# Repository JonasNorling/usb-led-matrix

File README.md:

A USB connected LED matrix
==========================

This is a quick holidays project from 2020/2021. It is a 8×8 SMD LED matrix board with a STM32G4 and USB-C connector.

What it does is up to the software but currently I use it to display CPU load on my PC. When not connected to a USB host it displays a calm animation.

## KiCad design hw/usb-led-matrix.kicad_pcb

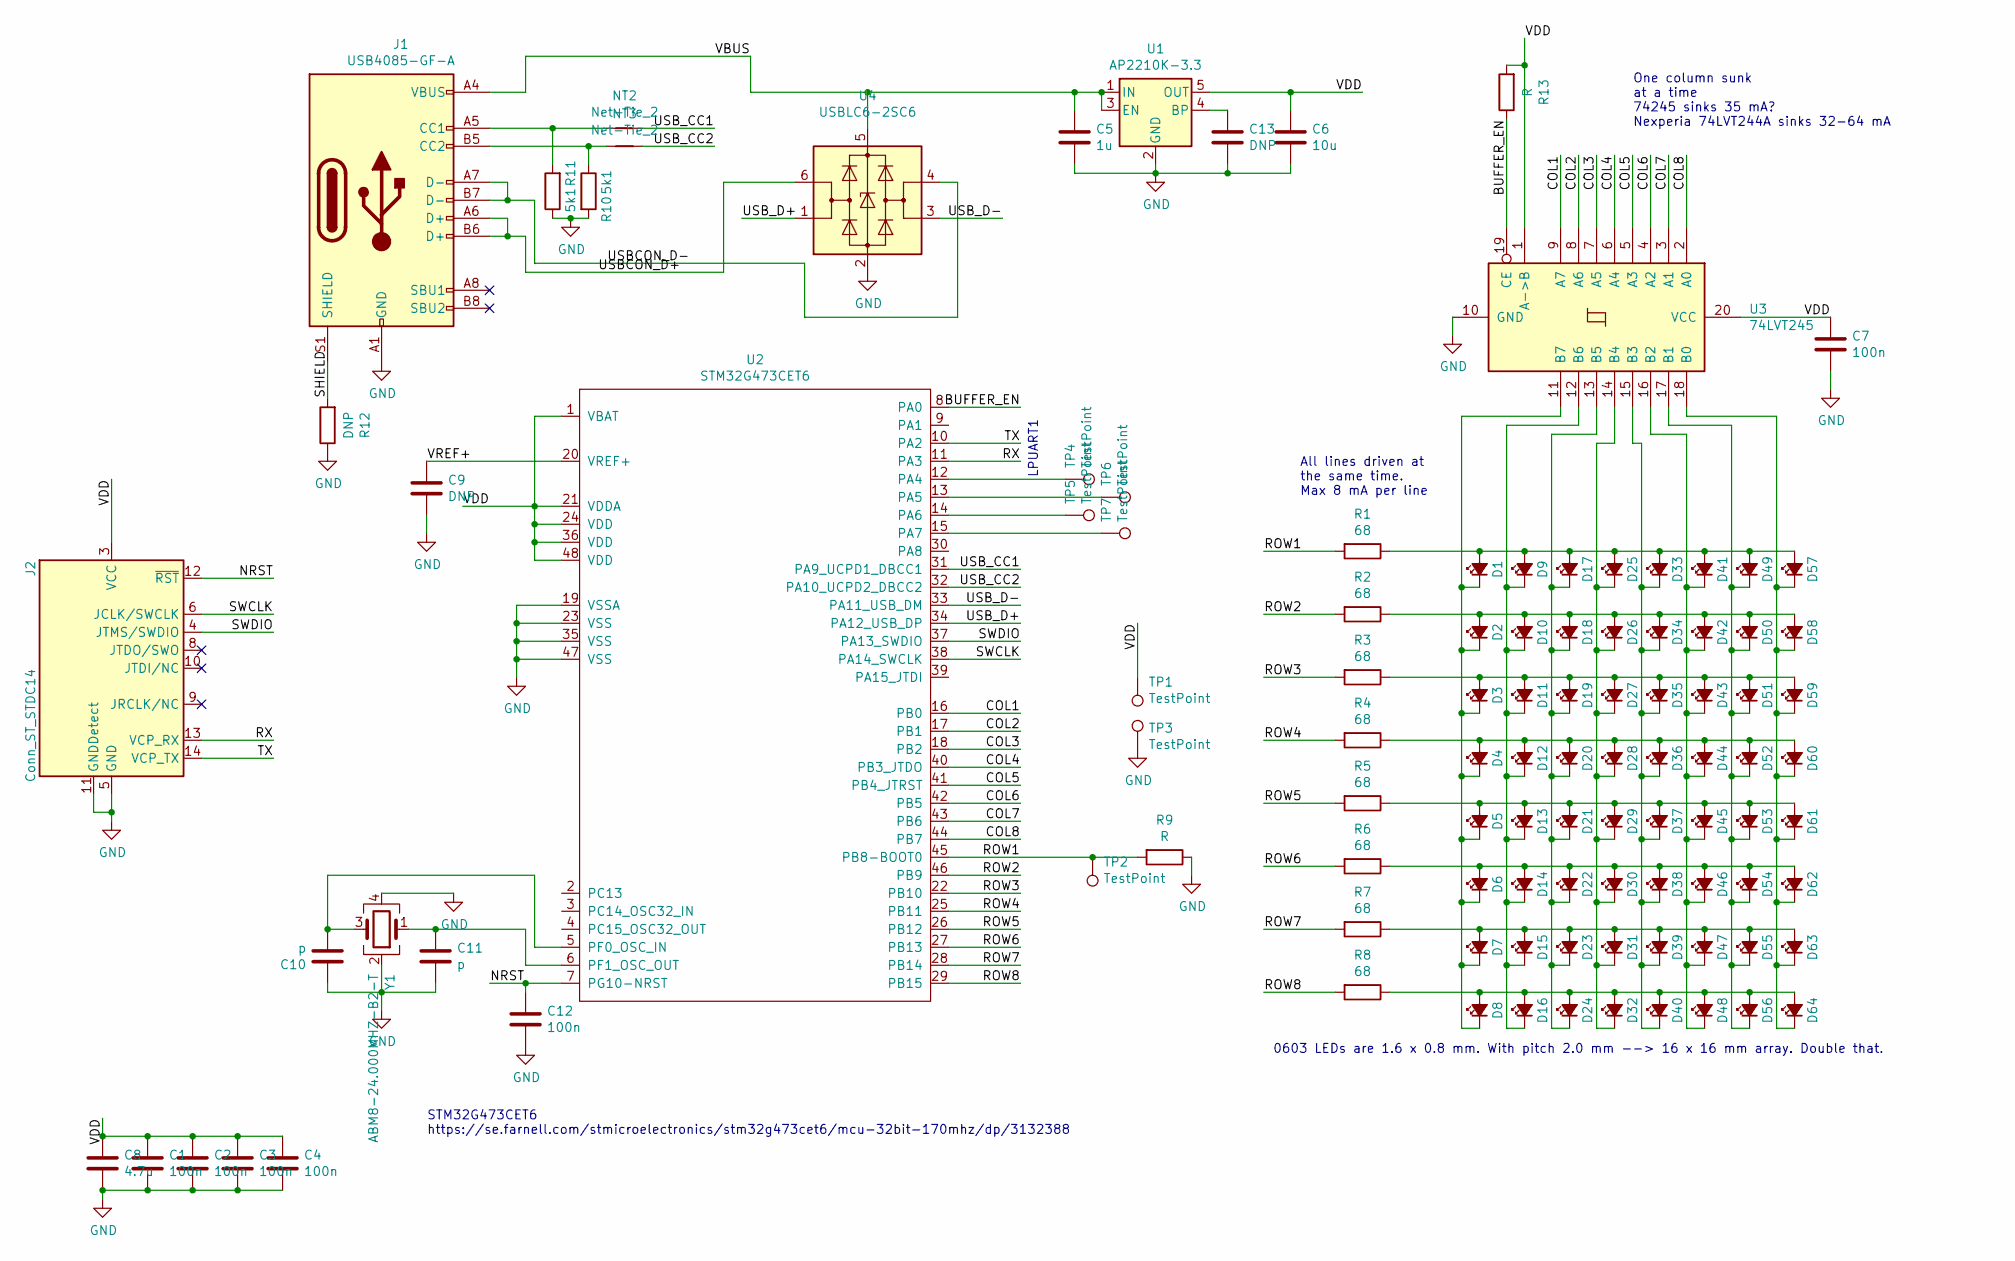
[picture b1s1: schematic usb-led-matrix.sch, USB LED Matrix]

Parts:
C1, C2, C3, C4, C7, C12: 100n; C_0402_1005Metric_Pad0.74x0.62mm_HandSolder
C5: 1u; C_0603_1608Metric_Pad1.08x0.95mm_HandSolder
C6: 10u; C_0603_1608Metric_Pad1.08x0.95mm_HandSolder
C8: 4.7u; C_0603_1608Metric_Pad1.08x0.95mm_HandSolder
C9, C13: DNP; C_0402_1005Metric_Pad0.74x0.62mm_HandSolder
C10, C11: p; C_0402_1005Metric_Pad0.74x0.62mm_HandSolder
D1, D2, D3, D4, D5, D6, D7, D8, D9, D10, D11, D12, D13, D14, D15, D16, D17, D18, D19, D20, D21, D22, D23, D24, D25, D26, D27, D28, D29, D30, D31, D32, D33, D34, D35, D36, D37, D38, D39, D40, D41, D42, D43, D44, D45, D46, D47, D48, D49, D50, D51, D52, D53, D54, D55, D56, D57, D58, D59, D60, D61, D62, D63, D64: LED_Small_ALT; LED_0603_1608Metric
J1: USB4085-GF-A; USB_C_Receptacle_GCT_USB4085
J2: Conn_ST_STDC14; PinHeader_2x07_P1.27mm_Vertical_SMD
NT2, NT3: Net-Tie_2; R_0201_0603Metric
R1, R2, R3, R4, R5, R6, R7, R8: 68; R_0402_1005Metric_Pad0.72x0.64mm_HandSolder
R9, R13: R; R_0402_1005Metric_Pad0.72x0.64mm_HandSolder
R10, R11: 5k1; R_0402_1005Metric_Pad0.72x0.64mm_HandSolder
R12: DNP; R_0402_1005Metric_Pad0.72x0.64mm_HandSolder
TP1, TP2, TP3: TestPoint; TestPoint_THTPad_D1.0mm_Drill0.5mm
TP4, TP5, TP6, TP7: TestPoint; TestPoint_Pad_1.0x1.0mm
U1: AP2210K-3.3; SOT-23-5
U2: STM32G473CET6; LQFP-48_7x7mm_P0.5mm
U3: 74LVT245; TSSOP-20_4.4x6.5mm_P0.65mm
U4: USBLC6-2SC6; SOT-23-6
Y1: ABM8-24.000MHZ-B2-T; Crystal_SMD_3225-4Pin_3.2x2.5mm

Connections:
/BUFFER_EN: R13.1, U2.8 (PA0), U3.19 (CE)
/COL1: U2.16 (PB0), U3.9 (A7)
/COL2: U2.17 (PB1), U3.8 (A6)
/COL3: U2.18 (PB2), U3.7 (A5)
/COL4: U2.40 (PB3_JTDO), U3.6 (A4)
/COL5: U2.41 (PB4_JTRST), U3.5 (A3)
/COL6: U2.42 (PB5), U3.4 (A2)
/COL7: U2.43 (PB6), U3.3 (A1)
/COL8: U2.44 (PB7), U3.2 (A0)
/NRST: C12.1, J2.12 (~RST), U2.7 (PG10-NRST)
/ROW1: R1.2, R9.2, TP2.1, U2.45 (PB8-BOOT0)
/ROW2: R2.2, U2.46 (PB9)
/ROW3: R3.2, U2.22 (PB10)
/ROW4: R4.2, U2.25 (PB11)
/ROW5: R5.2, U2.26 (PB12)
/ROW6: R6.2, U2.27 (PB13)
/ROW7: R7.2, U2.28 (PB14)
/ROW8: R8.2, U2.29 (PB15)
/RX: J2.13 (VCP_RX), U2.11 (PA3)
/SHIELD: J1.S1 (SHIELD), R12.2
/SWCLK: J2.6 (JCLK/SWCLK), U2.38 (PA14_SWCLK)
/SWDIO: J2.4 (JTMS/SWDIO), U2.37 (PA13_SWDIO)
/TX: J2.14 (VCP_TX), U2.10 (PA2)
/USBCON_D+: J1.A6 (D+), J1.B6 (D+), U4.6 (I/O1)
/USBCON_D-: J1.A7 (D-), J1.B7 (D-), U4.4 (I/O2)
/USB_CC1: NT2.2, U2.31 (PA9_UCPD1_DBCC1)
/USB_CC2: NT3.2, U2.32 (PA10_UCPD2_DBCC2)
/USB_D+: U2.34 (PA12_USB_DP), U4.1 (I/O1)
/USB_D-: U2.33 (PA11_USB_DM), U4.3 (I/O2)
/VBUS: C5.1, J1.A4 (VBUS), J1.A9 (VBUS), J1.B4 (VBUS), J1.B9 (VBUS), U1.1 (IN), U1.3 (EN), U4.5 (VBUS)
/VDD: C1.1, C2.1, C3.1, C4.1, C6.1, C7.1, C8.1, J2.3 (VCC), R13.2, TP1.1, U1.5 (OUT), U2.1 (VBAT), U2.21 (VDDA), U2.24 (VDD), U2.36 (VDD), U2.48 (VDD), U3.1 (A->B), U3.20 (VCC)
/VREF+: C9.1, U2.20 (VREF+)
GND: C1.2, C2.2, C3.2, C4.2, C5.2, C6.2, C7.2, C8.2, C9.2, C10.1, C11.2, C12.2, C13.2, J1.A1 (GND), J1.A12 (GND), J1.B1 (GND), J1.B12 (GND), J2.5 (GND), J2.7 (GND), J2.11 (GNDDetect), R9.1, R10.2, R11.1, R12.1, TP3.1, U1.2 (GND), U2.19 (VSSA), U2.23 (VSS), U2.35 (VSS), U2.47 (VSS), U3.10 (GND), U4.2 (GND), Y1.2, Y1.4
unnamed: C10.2, U2.5 (PF0_OSC_IN), Y1.3
unnamed: C11.1, U2.6 (PF1_OSC_OUT), Y1.1
unnamed: C13.1, U1.4 (BP)
unnamed: D1.1 (K), D2.1 (K), D3.1 (K), D4.1 (K), D5.1 (K), D6.1 (K), D7.1 (K), D8.1 (K), U3.11 (B7)
unnamed: D1.2 (A), D9.2 (A), D17.2 (A), D25.2 (A), D33.2 (A), D41.2 (A), D49.2 (A), D57.2 (A), R1.1
unnamed: D9.1 (K), D10.1 (K), D11.1 (K), D12.1 (K), D13.1 (K), D14.1 (K), D15.1 (K), D16.1 (K), U3.12 (B6)
unnamed: D2.2 (A), D10.2 (A), D18.2 (A), D26.2 (A), D34.2 (A), D42.2 (A), D50.2 (A), D58.2 (A), R2.1
unnamed: D3.2 (A), D11.2 (A), D19.2 (A), D27.2 (A), D35.2 (A), D43.2 (A), D51.2 (A), D59.2 (A), R3.1
unnamed: D4.2 (A), D12.2 (A), D20.2 (A), D28.2 (A), D36.2 (A), D44.2 (A), D52.2 (A), D60.2 (A), R4.1
unnamed: D5.2 (A), D13.2 (A), D21.2 (A), D29.2 (A), D37.2 (A), D45.2 (A), D53.2 (A), D61.2 (A), R5.1
unnamed: D6.2 (A), D14.2 (A), D22.2 (A), D30.2 (A), D38.2 (A), D46.2 (A), D54.2 (A), D62.2 (A), R6.1
unnamed: D7.2 (A), D15.2 (A), D23.2 (A), D31.2 (A), D39.2 (A), D47.2 (A), D55.2 (A), D63.2 (A), R7.1
unnamed: D8.2 (A), D16.2 (A), D24.2 (A), D32.2 (A), D40.2 (A), D48.2 (A), D56.2 (A), D64.2 (A), R8.1
unnamed: D17.1 (K), D18.1 (K), D19.1 (K), D20.1 (K), D21.1 (K), D22.1 (K), D23.1 (K), D24.1 (K), U3.13 (B5)
unnamed: D25.1 (K), D26.1 (K), D27.1 (K), D28.1 (K), D29.1 (K), D30.1 (K), D31.1 (K), D32.1 (K), U3.14 (B4)
unnamed: D33.1 (K), D34.1 (K), D35.1 (K), D36.1 (K), D37.1 (K), D38.1 (K), D39.1 (K), D40.1 (K), U3.15 (B3)
unnamed: D41.1 (K), D42.1 (K), D43.1 (K), D44.1 (K), D45.1 (K), D46.1 (K), D47.1 (K), D48.1 (K), U3.16 (B2)
unnamed: D49.1 (K), D50.1 (K), D51.1 (K), D52.1 (K), D53.1 (K), D54.1 (K), D55.1 (K), D56.1 (K), U3.17 (B1)
unnamed: D57.1 (K), D58.1 (K), D59.1 (K), D60.1 (K), D61.1 (K), D62.1 (K), D63.1 (K), D64.1 (K), U3.18 (B0)
unnamed: J1.A5 (CC1), NT2.1, R11.2
unnamed: J1.B5 (CC2), NT3.1, R10.1
unnamed: TP4.1, U2.12 (PA4)
unnamed: TP5.1, U2.14 (PA6)
unnamed: TP6.1, U2.13 (PA5)
unnamed: TP7.1, U2.15 (PA7)

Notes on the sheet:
All lines driven at the same time. Max 8 mA per line
One column sunk at a time 74245 sinks 35 mA? Nexperia 74LVT244A sinks 32-64 mA
STM32G473CET6 https://se.farnell.com/stmicroelectronics/stm32g473cet6/mcu-32bit-170mhz/dp/3132388
0603 LEDs are 1.6 x 0.8 mm. With pitch 2.0 mm --> 16 x 16 mm array. Double that.
LPUART1

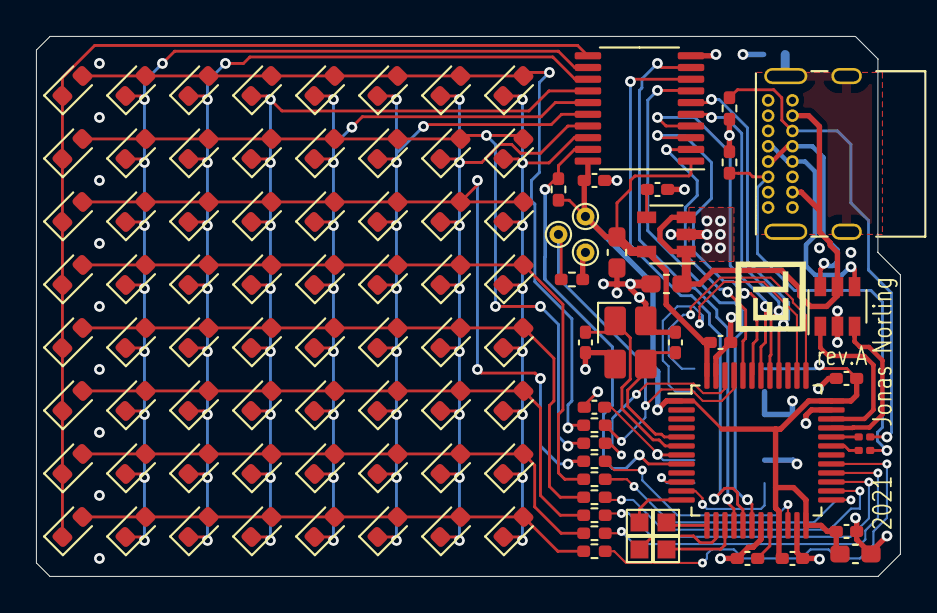
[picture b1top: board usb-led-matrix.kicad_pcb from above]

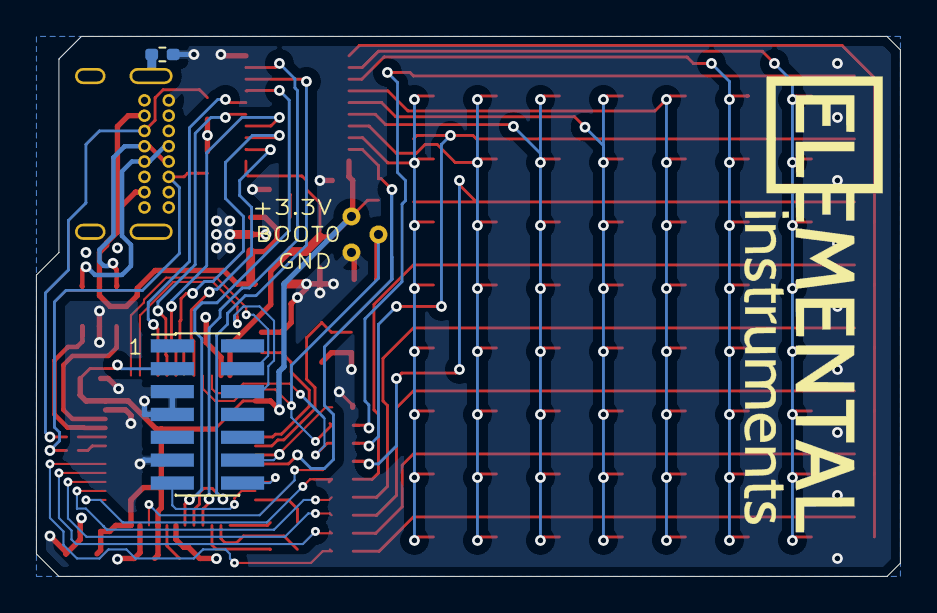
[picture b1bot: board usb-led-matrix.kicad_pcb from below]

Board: 4 copper layers, 48.0 x 30.0 mm, 106 parts (2 on the bottom side), 58 nets.

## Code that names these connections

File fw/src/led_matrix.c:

#include <zephyr.h>
#include <drivers/gpio.h>
#include <logging/log.h>
#include <irq.h>
#include <soc.h>
#include <stdio.h>
#include <stdlib.h>
#include <math.h>
#include <stm32_ll_tim.h>

#include "led_matrix.h"

LOG_MODULE_REGISTER(led_matrix);

#define TIMER TIM1
#if CONFIG_SOC_SERIES_STM32G4X
#define IRQ_NUMBER TIM1_UP_TIM16_IRQn
#elif CONFIG_SOC_SERIES_STM32F4X
#define IRQ_NUMBER TIM1_UP_TIM10_IRQn
#endif

#define GPIO_PIN(dt_node, flags) { DT_GPIO_LABEL(dt_node, gpios), \
                                   DT_GPIO_PIN(dt_node, gpios), \
                                   (flags) | DT_GPIO_FLAGS(dt_node, gpios) }

struct pin_definition {
    const char *devname;
    gpio_pin_t pin;
    gpio_flags_t flags;
};

struct pin {
    const struct device *device;
    gpio_pin_t pin;
};

#define PIN_TP4 17

static const struct pin_definition pin_definitions[] = {
#if DT_NODE_HAS_STATUS(DT_PATH(matrix, buffer_en), okay)
    GPIO_PIN(DT_PATH(matrix, buffer_en), GPIO_OUTPUT_ACTIVE),
    GPIO_PIN(DT_PATH(matrix, row1), GPIO_OUTPUT_INACTIVE),
    GPIO_PIN(DT_PATH(matrix, row2), GPIO_OUTPUT_INACTIVE),
    GPIO_PIN(DT_PATH(matrix, row3), GPIO_OUTPUT_INACTIVE),
    GPIO_PIN(DT_PATH(matrix, row4), GPIO_OUTPUT_INACTIVE),
    GPIO_PIN(DT_PATH(matrix, row5), GPIO_OUTPUT_INACTIVE),
    GPIO_PIN(DT_PATH(matrix, row6), GPIO_OUTPUT_INACTIVE),
    GPIO_PIN(DT_PATH(matrix, row7), GPIO_OUTPUT_INACTIVE),
    GPIO_PIN(DT_PATH(matrix, row8), GPIO_OUTPUT_INACTIVE),
    GPIO_PIN(DT_PATH(matrix, col1), GPIO_OUTPUT_INACTIVE),
    GPIO_PIN(DT_PATH(matrix, col2), GPIO_OUTPUT_INACTIVE),
    GPIO_PIN(DT_PATH(matrix, col3), GPIO_OUTPUT_INACTIVE),
    GPIO_PIN(DT_PATH(matrix, col4), GPIO_OUTPUT_INACTIVE),
    GPIO_PIN(DT_PATH(matrix, col5), GPIO_OUTPUT_INACTIVE),
    GPIO_PIN(DT_PATH(matrix, col6), GPIO_OUTPUT_INACTIVE),
    GPIO_PIN(DT_PATH(matrix, col7), GPIO_OUTPUT_INACTIVE),
    GPIO_PIN(DT_PATH(matrix, col8), GPIO_OUTPUT_INACTIVE),
    [PIN_TP4] = GPIO_PIN(DT_PATH(testpoints, tp4), GPIO_OUTPUT_INACTIVE),
    GPIO_PIN(DT_PATH(testpoints, tp5), GPIO_INPUT),
    GPIO_PIN(DT_PATH(testpoints, tp6), GPIO_INPUT),
    GPIO_PIN(DT_PATH(testpoints, tp7), GPIO_INPUT),
#elif DT_NODE_HAS_STATUS(DT_ALIAS(led0), okay)
    GPIO_PIN(DT_ALIAS(led0), GPIO_OUTPUT_INACTIVE),
    GPIO_PIN(DT_ALIAS(led1), GPIO_OUTPUT_INACTIVE),
    GPIO_PIN(DT_ALIAS(led2), GPIO_OUTPUT_INACTIVE),
    GPIO_PIN(DT_ALIAS(led3), GPIO_OUTPUT_INACTIVE),
#else
#warning Building without LED matrix support
#endif
};

static struct pin pins[ARRAY_SIZE(pin_definitions)];
static uint8_t led_data[LED_COUNT];
static uint64_t last_usb_active;

static uint8_t get_led_state(int col, int row)
{
    return led_data[(row * 8) + (col % 8)];
}

#if CONFIG_SOC_FAMILY_STM32
static void timer_isr(const void *arg)
{
    gpio_pin_set(pins[PIN_TP4].device, pins[PIN_TP4].pin, true);
    LL_TIM_ClearFlag_UPDATE(TIMER);

    static uint8_t counter = 0;
    counter++;

    const uint8_t colno = counter % 8;
    const uint8_t pwm = (counter / 8) % 16;

    uint8_t row = 0;
    for (int rowno = 0; rowno < 8; rowno++) {
        const uint8_t intensity = get_led_state(colno, rowno);
        const bool on = intensity > pwm;
        row |= on ? (1 << rowno) : 0;
    }

    const uint8_t colbits = 1 << colno;
    gpio_port_set_masked(pins[1].device, 0xffff, (row << 8) | colbits);
    gpio_pin_set(pins[PIN_TP4].device, pins[PIN_TP4].pin, false);
}
#endif

void led_matrix_init(void)
{
    LOG_INF("Setting up LED matrix");
    for (int i = 0; i < ARRAY_SIZE(pin_definitions); i++) {
        pins[i].device = device_get_binding(pin_definitions[i].devname);
        pins[i].pin = pin_definitions[i].pin;
        if (!pins[i].device) {
            LOG_ERR("No device");
            return;
        }
        int rc = gpio_pin_configure(pins[i].device,
                                    pin_definitions[i].pin,
                                    pin_definitions[i].flags);
        if (rc) {
            LOG_ERR("Configure failed");
            return;
        }
    }

    led_data[0] = 1;

#if CONFIG_SOC_FAMILY_STM32
    IRQ_CONNECT(IRQ_NUMBER, 2, timer_isr, NULL, 0);
    irq_enable(IRQ_NUMBER);

    __HAL_RCC_TIM1_CLK_ENABLE();
    LL_TIM_InitTypeDef init;
    LL_TIM_StructInit(&init);
    init.Prescaler = 1;
    init.Autoreload = 256;
    LL_TIM_Init(TIMER, &init);
    LL_TIM_EnableIT_UPDATE(TIMER);
#endif
}

static void test_patterns()
{
    uint8_t data[LED_COUNT];

    // All on
    memset(data, 0xff, sizeof(data));
    led_matrix_set(data, LED_COUNT);
    k_sleep(K_MSEC(500));

    // Fade out
    for (int i = 8; i >= 0; i--) {
        memset(data, i, sizeof(data));
        led_matrix_set(data, LED_COUNT);
        k_sleep(K_MSEC(100));
    }

    // Rows
    for (int row = 0; row < 8; row++) {
        memset(data, 0x00, sizeof(data));
        for (int col = 0; col < 8; col++) {
            data[(row * 8) + (col % 8)] = 1;
        }
        led_matrix_set(data, LED_COUNT);
        k_sleep(K_MSEC(125));
    }

    // Columns
    for (int col = 0; col < 8; col++) {
        memset(data, 0x00, sizeof(data));
        for (int row = 0; row < 8; row++) {
            data[(row * 8) + (col % 8)] = 1;
        }
        led_matrix_set(data, LED_COUNT);
        k_sleep(K_MSEC(125));
    }

    // A cross
    for (int col = 0; col < 8; col++) {
        for (int row = 0; row < 8; row++) {
            data[(row * 8) + (col % 8)] = ((row - col) == 0) || ((row + col) == 7) ;
        }
    }
    led_matrix_set(data, LED_COUNT);
}

static uint8_t craprand(void)
{
    static unsigned v = 1;
    v = (1103515245 * v + 12345);
    return v >> 24;
}

static float absolute(float v)
{
    if (v < 0) return -v;
    return v;
}

#define KSZ 5
static float get(float frame[8][8], int x, int y)
{
    if (x < 0) return 0.0;
    if (y < 0) return 0.0;
    if (x >= 8) return 0.0;
    if (y >= 8) return 0.0;
    return frame[x][y];
}

static void step_animation(void)
{
    static float kernel[KSZ][KSZ] = {
        {    0, 0.01,    0,  0.00, 0.00 },
        {    0,-0.01,  0.1, -0.08,    0 },
        {    0, 0.09,  0.8,   0.1, 0.01 },
        {    0,-0.01,  0.1, -0.08,    0 },
        {    0, 0.01,    0,  0.00, 0.00 },
    };
    static float frame[8][8] = {{ 0 },
                                { 0 },
                                { 0 },
                                { 20.0, 0, 0, 0, 0 }};
    float next_frame[8][8];
    const float fudge = 0.998;

    for (int row = 0; row < 8; row++) {
        for (int col = 0; col < 8; col++) {
            float v = 0;
            for (int x = 0; x < KSZ; x++) {
                for (int y = 0; y < KSZ; y++) {
                    v += get(frame, col + x - KSZ/2, row + y - KSZ/2) * kernel[x][y];
                }
            }
            next_frame[col][row] = v * fudge;
        }
    }

    uint8_t buffer[LED_COUNT];
    float total = 0;
    for (int row = 0; row < 8; row++) {
        for (int col = 0; col < 8; col++) {
            buffer[(row * 8) + (col % 8)] = absolute(next_frame[col][row]);
            if (absolute(next_frame[col][row]) > 15) {
                next_frame[col][row] = 5;
            }
            frame[col][row] = next_frame[col][row];
            total += absolute(next_frame[col][row]);
        }
    }

    memcpy(led_data, buffer, sizeof(led_data));

    if (total < 70.0f) {
        int x = craprand() % 8;
        int y = craprand() % 8;
        frame[x][y] = 20.0;
        LOG_INF("Spawn at %d %d", x ,y);
    }
#if CONFIG_BOARD_NATIVE_POSIX
    printf("total=%.3f\n", total);
    for (int row = 0; row < 8; row++) {
        for (int col = 0; col < 8; col++) {
            const char c[9] = { ' ', '1', '2', '3', '4', '5', '6', '7', '@' };
            int v = get_led_state(row, col);
            if (v < 0) v = 0;
            if (v > 8) v = 8;
            printf("%c ", c[v]);
        }
        printf("\n");
    }
    printf("----------------\n");
#endif
}

void led_matrix_start(void)
{
#if CONFIG_SOC_FAMILY_STM32
    LL_TIM_EnableCounter(TIMER);
#endif

    test_patterns();
    while (true) {
        if (k_uptime_get() > last_usb_active + 2000) {
            step_animation();
        }
        k_sleep(K_MSEC(20));
    }
}

void led_matrix_set(const uint8_t *data, size_t len)
{
    memcpy(led_data, data, MIN(len, sizeof(led_data)));
    last_usb_active = k_uptime_get();
}

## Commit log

2020-12-27 Initial
2020-12-27 Board
2020-12-27 Script to make LED array
2020-12-27 Work
2020-12-29 USB-C connector
2020-12-31 Schematic updates
    - TVS on USB
    - SOT23-5 vreg
    - 100n on NRST
    - SWO hooked up
    - Caps on crystal
2020-12-31 Connect more USB signals
2020-12-31 Initial firmware project
2020-12-31 Four-layer board, update routing and some components
2020-12-31 Rearrange pins
2021-01-01 Update routing
2021-01-01 Use custom board
    Copied and slightly adapted from NUCLEO-G474RE.
2021-01-01 Set LEDs
2021-01-01 PCB updates
2021-01-01 USB code?
2021-01-03 Make it build on native_posix
2021-01-05 Mouse movement
2021-01-06 Add missing KiCad libraries
2021-01-06 Fine tune PCB, silkscreen rev.A
2021-01-09 hidraw program sending OUT reports
2021-01-09 Rearrange sources
2021-01-09 HID descriptor
2021-01-09 Set LED states?
2021-01-10 Maybe show CPU load
2021-01-16 Fix timing in hidraw program
2021-01-23 Update SDK, flash with openocd
2021-01-23 Enable HSI trim if using HSI, enable debug in sleep
2021-01-23 Fix bug in led_matrix.c
2021-01-24 Use HSI
2021-01-25 Timer interrupt controlling LEDs
2021-01-25 udev rules
2021-01-25 Fixes
2021-01-27 Start with a test pattern
2021-02-05 Output fractional brightness
2021-02-05 LED control
2021-02-06 Toggle test point in ISR
2021-02-06 Animation
2021-02-06 Nicer animation?
2021-02-09 Fix broken randomnes
2021-03-14 USB activity check
2021-03-14 Add README and include a header for building against vanilla Zephyr
2021-03-14 Add MIT license
2021-03-14 Program brown-out reset
2021-03-14 Upgrade to Zephyr 2.5, moving pinmux into DTS
2021-03-14 Picture of the board
2021-05-08 Scan for right hidraw device
2021-11-03 Wait for USB device to be plugged in
